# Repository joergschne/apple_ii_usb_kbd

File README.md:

# Apple II USB Keyboard-Adapter

Based on Arduino-UNO (ATMEGA328P) and Maxim MAX3421E USB-Host-Controller

- USB keyboard (wireless) with and without NKRO (N-Key-Rollover) support.

- DE and US layouts can be toggled by pressing Windows+1 (US) and Windows+2 (DE). Windows+0 stores the last setting in EEPROM.

- Ctrl+Insert / Ctrl+Alt+Delete performs a hardware reset.

- The Windows key itself switches back to the original Apple keyboard. This is the default setting on power up and the switch to USB is automatic.

- Autorepeat function and the “Up arrow” button repeats the last entry

- Caps Lock (Shift Lock) lower case support

- Win+9 (LodeRunner Mapping) assigns the keys I,J,K,L to W,A,S,D to play an unpatched version of LodeRunner with the usual key combination

- Specially build for: CHERRY MX-LP 2.1 Compact Wireless Keyboard

APPLE II forever!

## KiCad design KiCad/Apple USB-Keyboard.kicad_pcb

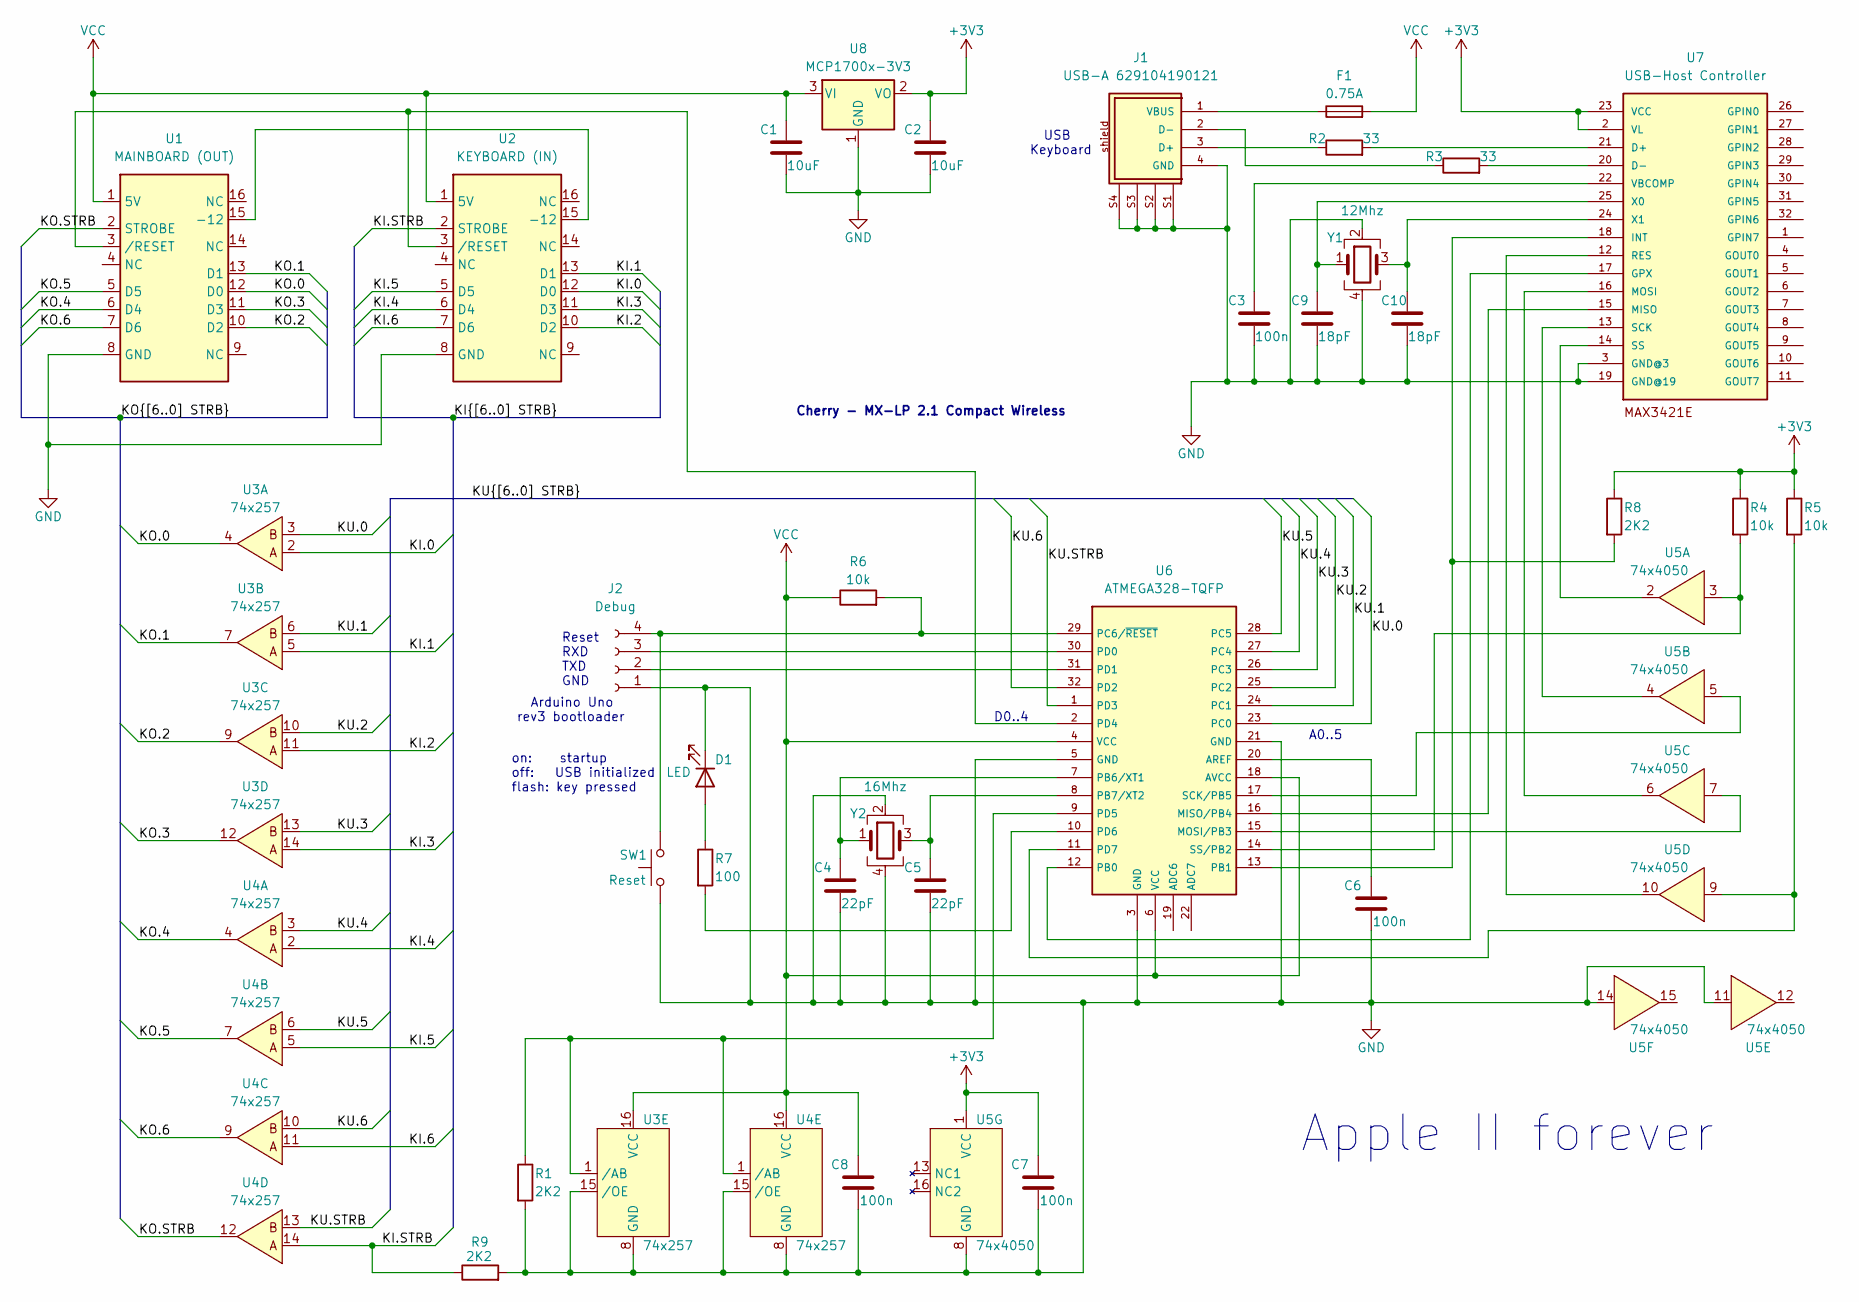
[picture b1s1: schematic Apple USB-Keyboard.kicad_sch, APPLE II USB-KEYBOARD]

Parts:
C1, C2: 10uF; C_0805_2012Metric_Pad1.18x1.45mm_HandSolder
C3, C6, C7, C8: 100n; C_0805_2012Metric_Pad1.18x1.45mm_HandSolder
C4, C5: 22pF; C_0805_2012Metric_Pad1.18x1.45mm_HandSolder
C9, C10: 18pF; C_0805_2012Metric_Pad1.18x1.45mm_HandSolder
D1: LED; LED_D3.0mm
F1: 0.75A; Fuse_0805_2012Metric_Pad1.15x1.40mm_HandSolder
J1: USB-A 629104190121; PART-NUMBER 629104190121
J2: Debug; PinHeader_1x04_P2.54mm_Horizontal
R1, R8, R9: 2K2; R_0805_2012Metric_Pad1.20x1.40mm_HandSolder
R2, R3: 33; R_0805_2012Metric_Pad1.20x1.40mm_HandSolder
R4, R5, R6: 10k; R_0805_2012Metric_Pad1.20x1.40mm_HandSolder
R7: 100; R_0805_2012Metric_Pad1.20x1.40mm_HandSolder
SW1: Reset; SW_PTS525SM15SMTR2LFS
U1: MAINBOARD (OUT); DIP-16_W7.62mm_Socket_LongPads
U2: KEYBOARD (IN); DIP-16_W7.62mm_Socket_LongPads
U3, U4: 74x257; SOIC-16_3.9x9.9mm_P1.27mm
U5: 74x4050; SOIC-16_3.9x9.9mm_P1.27mm
U6: ATMEGA328-TQFP; TQFP-32_7x7mm_P0.8mm
U7: USB-Host Controller; max3421-TQFP
U8: MCP1700x-3V3; SOT-23
Y1: 12Mhz; FA238
Y2: 16Mhz; FA238

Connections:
+3V3: C2.1, C7.2, R4.1, R5.1, R8.1, U5.1 (VCC), U7.2 (VL), U7.23 (VCC), U8.2 (VO)
/KI.0: U2.12 (D0), U3.2
/KI.1: U2.13 (D1), U3.5
/KI.2: U2.10 (D2), U3.11
/KI.3: U2.11 (D3), U3.14
/KI.4: U2.6 (D4), U4.2
/KI.5: U2.5 (D5), U4.5
/KI.6: U2.7 (D6), U4.11
/KI.STRB: R9.1, U2.2 (STROBE), U4.14
/KO.0: U1.12 (D0), U3.4
/KO.1: U1.13 (D1), U3.7
/KO.2: U1.10 (D2), U3.9
/KO.3: U1.11 (D3), U3.12
/KO.4: U1.6 (D4), U4.4
/KO.5: U1.5 (D5), U4.7
/KO.6: U1.7 (D6), U4.9
/KO.STRB: U1.2 (STROBE), U4.12
/KU.0: U3.3, U6.23 (PC0)
/KU.1: U3.6, U6.24 (PC1)
/KU.2: U3.10, U6.25 (PC2)
/KU.3: U3.13, U6.26 (PC3)
/KU.4: U4.3, U6.27 (PC4)
/KU.5: U4.6, U6.28 (PC5)
/KU.6: U4.10, U6.32 (PD2)
/KU.STRB: U4.13, U6.1 (PD3)
GND: C1.2, C2.2, C3.2, C4.2, C5.2, C6.1, C7.1, C8.1, C9.2, C10.2, D1.1 (K), J1.4 (GND), J1.S1, J1.S2, J1.S3, J1.S4, J2.1, R1.2, R9.2, SW1.1, U1.8 (GND), U2.8 (GND), U3.8 (GND), U3.15 (/OE), U4.8 (GND), U4.15 (/OE), U5.8 (GND), U5.11, U5.14, U6.3 (GND), U6.5 (GND), U6.21 (GND), U7.3 (GND@3), U7.19 (GND@19), U8.1 (GND), Y1.2, Y1.4, Y2.2, Y2.4
unnamed: D1.2 (A), R7.1
unnamed: J1.3 (D+), R2.1
unnamed: J1.2 (D-), R3.1
unnamed: F1.1, J1.1 (VBUS)
unnamed: J2.2, U6.31 (PD1)
unnamed: J2.3, U6.30 (PD0)
unnamed: J2.4, R6.2, SW1.2, U6.29 (PC6/~RESET)
unnamed: U1.15 (-12), U2.15 (-12)
unnamed: U1.3 (/RESET), U2.3 (/RESET), U6.2 (PD4)
unnamed: R1.1, U3.1 (/AB), U4.1 (/AB), U6.9 (PD5)
unnamed: C6.2, U6.20 (AREF)
unnamed: U6.16 (MISO/PB4), U7.15 (MISO)
unnamed: U5.7, U6.15 (MOSI/PB3)
unnamed: U6.12 (PB0), U7.17 (GPX)
unnamed: R8.2, U6.13 (PB1), U7.18 (INT)
unnamed: C4.1, U6.7 (PB6/XT1), Y2.1
unnamed: C5.1, U6.8 (PB7/XT2), Y2.3
unnamed: R7.2, U6.10 (PD6)
unnamed: R5.2, U5.9, U6.11 (PD7)
unnamed: U5.5, U6.17 (SCK/PB5)
unnamed: R4.2, U5.3, U6.14 (SS/PB2)
unnamed: R2.2, U7.21 (D+)
unnamed: R3.2, U7.20 (D-)
unnamed: U5.6, U7.16 (MOSI)
unnamed: U5.10, U7.12 (RES)
unnamed: U5.4, U7.13 (SCK)
unnamed: U5.2, U7.14 (SS)
unnamed: C3.1, U7.22 (VBCOMP)
unnamed: C9.1, U7.25 (X0), Y1.1
unnamed: C10.1, U7.24 (X1), Y1.3
VCC: C1.1, C8.2, F1.2, R6.1, U1.1 (5V), U2.1 (5V), U3.16 (VCC), U4.16 (VCC), U6.4 (VCC), U6.6 (VCC), U6.18 (AVCC), U8.3 (VI)

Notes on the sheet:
D0..4
A0..5
Cherry - MX-LP 2.1 Compact Wireless
USB Keyboard
Arduino Uno rev3 bootloader
Reset RXD TXD GND
on: startup off: USB initialized flash: key pressed
Apple II forever

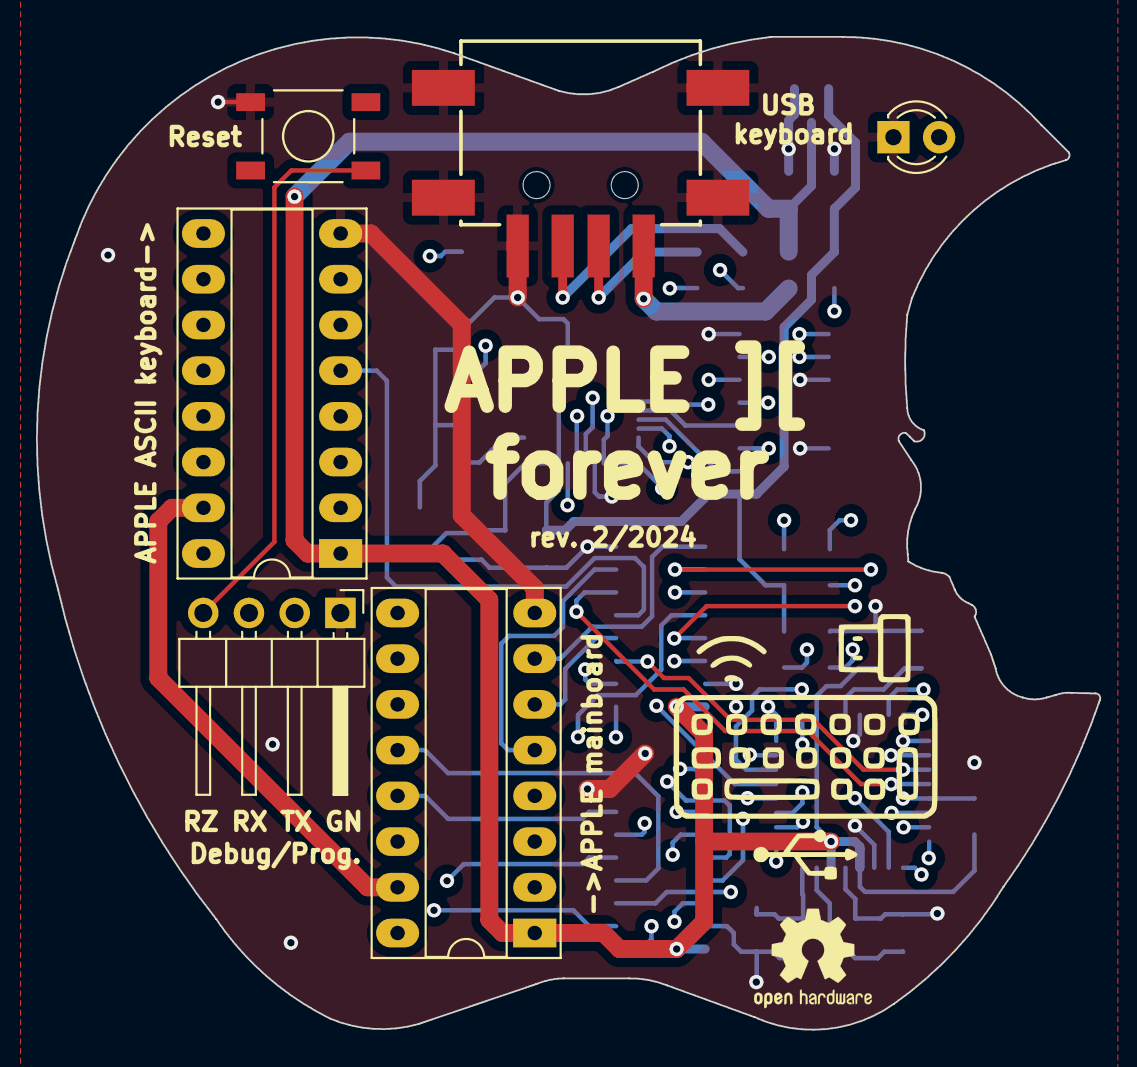
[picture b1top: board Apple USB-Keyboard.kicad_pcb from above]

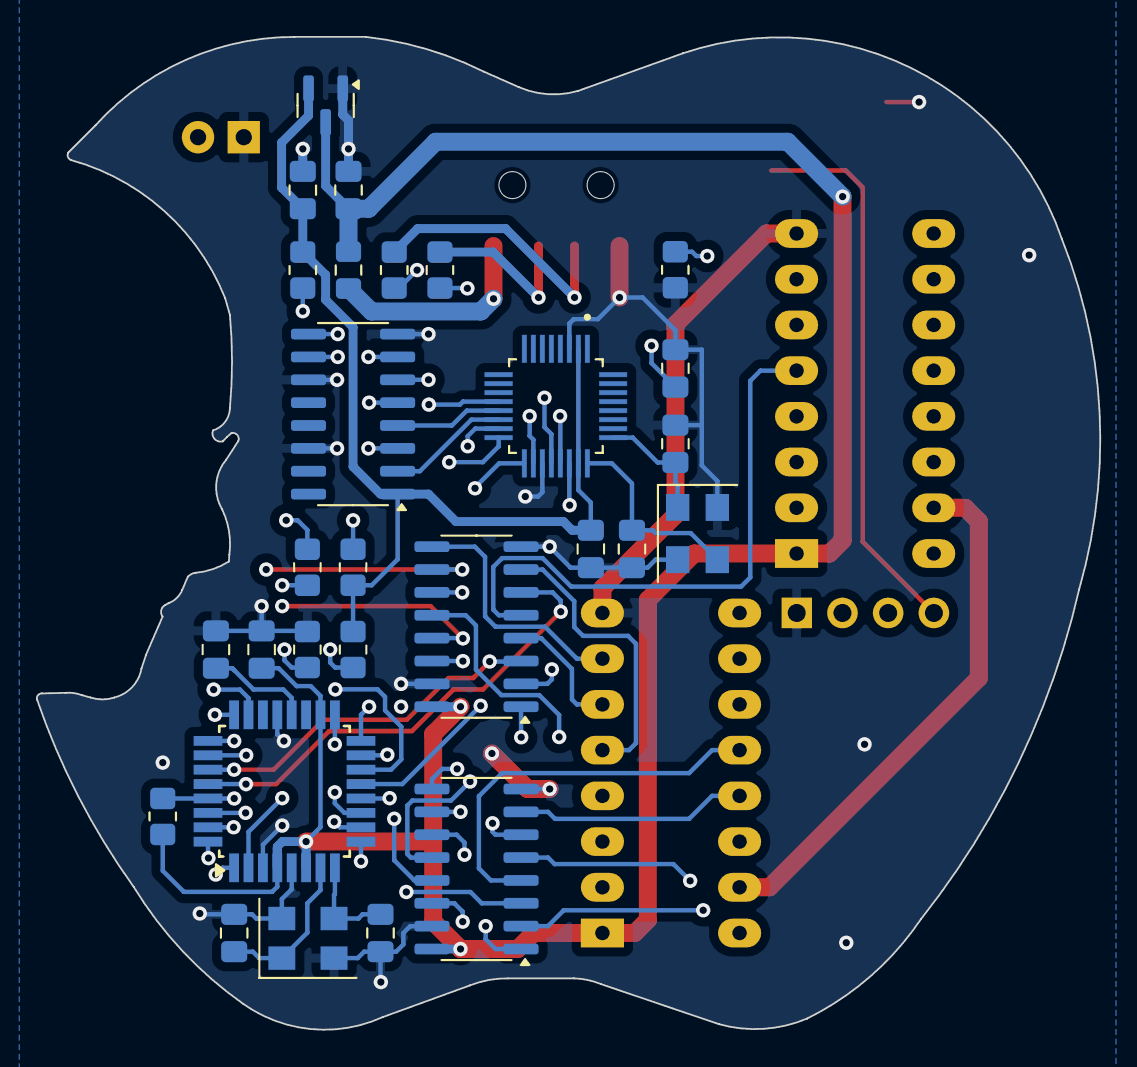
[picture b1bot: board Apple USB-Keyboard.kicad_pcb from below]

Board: 4 copper layers, 59.1 x 55.2 mm, 34 parts (28 on the bottom side), 57 nets.

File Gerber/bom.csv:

Designator,Footprint,Quantity,Value,LCSC Part #
"C1, C2",0805,2,10uF,
"C10, C9",0805,2,18pF,
"C3, C6, C7, C8",0805,4,100n,
"C4, C5",0805,2,22pF,
D1,LED_D3.0mm,1,LED,
F1,0805,1,0.75A,
J1,USB-A 629104190121,1,USB-A 629104190121,
J2,PinHeader_1x04_P2.54mm_Horizontal,1,Debug,
"R1, R8, R9",0805,3,2K2,
"R2, R3",0805,2,33,
"R4, R5, R6",0805,3,10k,
R7,0805,1,100,
SW1,SW_PTS525SM15SMTR2LFS,1,Reset,
U1,DIP-16_W7.62mm_Socket_LongPads,1,MAINBOARD (OUT),
U2,DIP-16_W7.62mm_Socket_LongPads,1,KEYBOARD (IN),
"U3, U4",SOIC-16_3.9x9.9mm_P1.27mm,2,74x257,
U5,SOIC-16_3.9x9.9mm_P1.27mm,1,74x4050,
U6,TQFP-32_7x7mm_P0.8mm,1,ATMEGA328-TQFP,
U7,max3421-TQFP,1,USB-Host Controller,
U8,SOT-23,1,MCP1700x-3V3,
Y1,FA238,1,12Mhz,
Y2,FA238,1,16Mhz,
